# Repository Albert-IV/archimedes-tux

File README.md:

# Archimedes Tux Keyboard

Based off the excellent [Architeuthis Dux keyboard](https://github.com/tapioki/cephalopoda/tree/main/Architeuthis%20dux), the goal is to add a third thumb key and see where else this takes me.

Built with [Ergogen](https://github.com/mrzealot/ergogen).

##### Rev 0.1 - Working!

* AllPCB came back asking about the drilling holes.  Apparently one of them went through one of the TRRS pads, so I told them to just not cut that one out. The rest of the drilling holes are not through any pads or anything important
* PCB's shipped
* PCB's Arrived and Built
* Confirmed working via QMK!

## Rev 0.2

**WIP** - Currently only in `output` folder and completely unrouted.

## Ideas / Goals

- [ ] Make Pro Micro footprint reversible
  - [x]  Add footprint to repo
  - [x]  Rotate footprint
  - [ ]  Add representation of the USB cutout / area
  - [ ]  Change pads / silks to match Ergogen
  - [ ]  Convert Kicad footprint to Erogogen footprint
  - [ ]  Add PR to Erogogen
  - [ ]  Add / place on board
- [ ] Support [[Nice!Nano]] and (possibly) [[BlueMicro]]
  - [ ]  On / Off switch for battery 
  - [ ]  Add battery soldering pads to 
- [ ] Mousebites on third thumb key?
- [ ] Change routing in bottom area to allow for larger silkscreen eye

v0.1 -> v0.2

- [x] Swap pins on row connections to make routing easier
- [x] Add reset switch / pads
- [x] Fix edge cuts / drilling.  (Tapi believes this is an issue due to the multiple fillets / outlines in the Ergogen script)
- [x] Rename repo / files
- [x] Re-add solder locations for switches instead of only hotswap
- [x] Rotate thumbs to allow 1.5u / 2u keycaps
- [x] Re-add Puck support
  - [x]  Add initial footprint to library
  - [x]  Fix text when rotation makes the text apppear in the wrong order
  - [x]  Make each individual screw hole able to be turned on / off
  - [x]  Add PR to Erogogen
  - [x]  Add / place puck on board
- [x] Mousebites on TRRS jack (removable TRRS socket for better [[Nice!Nano]] support)
  - [x] Did it a different way, but the same applies

### To Run Locally

**If you do not have Node.js installed** 

Install using [the installer](https://nodejs.org/en/download/) [NVM,](https://github.com/nvm-sh/nvm) or [Chocolatey](https://community.chocolatey.org/packages/nodejs-lts) depending on your platform.  Using the installer usually leads to permission issues with NPM so it's suggested to use either NVM or chocolatey if you don't want to mess with it too much.

Once this is installed run `npm i -g npm` to upgrade NPM to the latest version.

**After Node.js is installed**

Run `npm run patch-footprints` in the base directory.  This is updates one of the footprints to allow for SMD or through-hole only diodes.

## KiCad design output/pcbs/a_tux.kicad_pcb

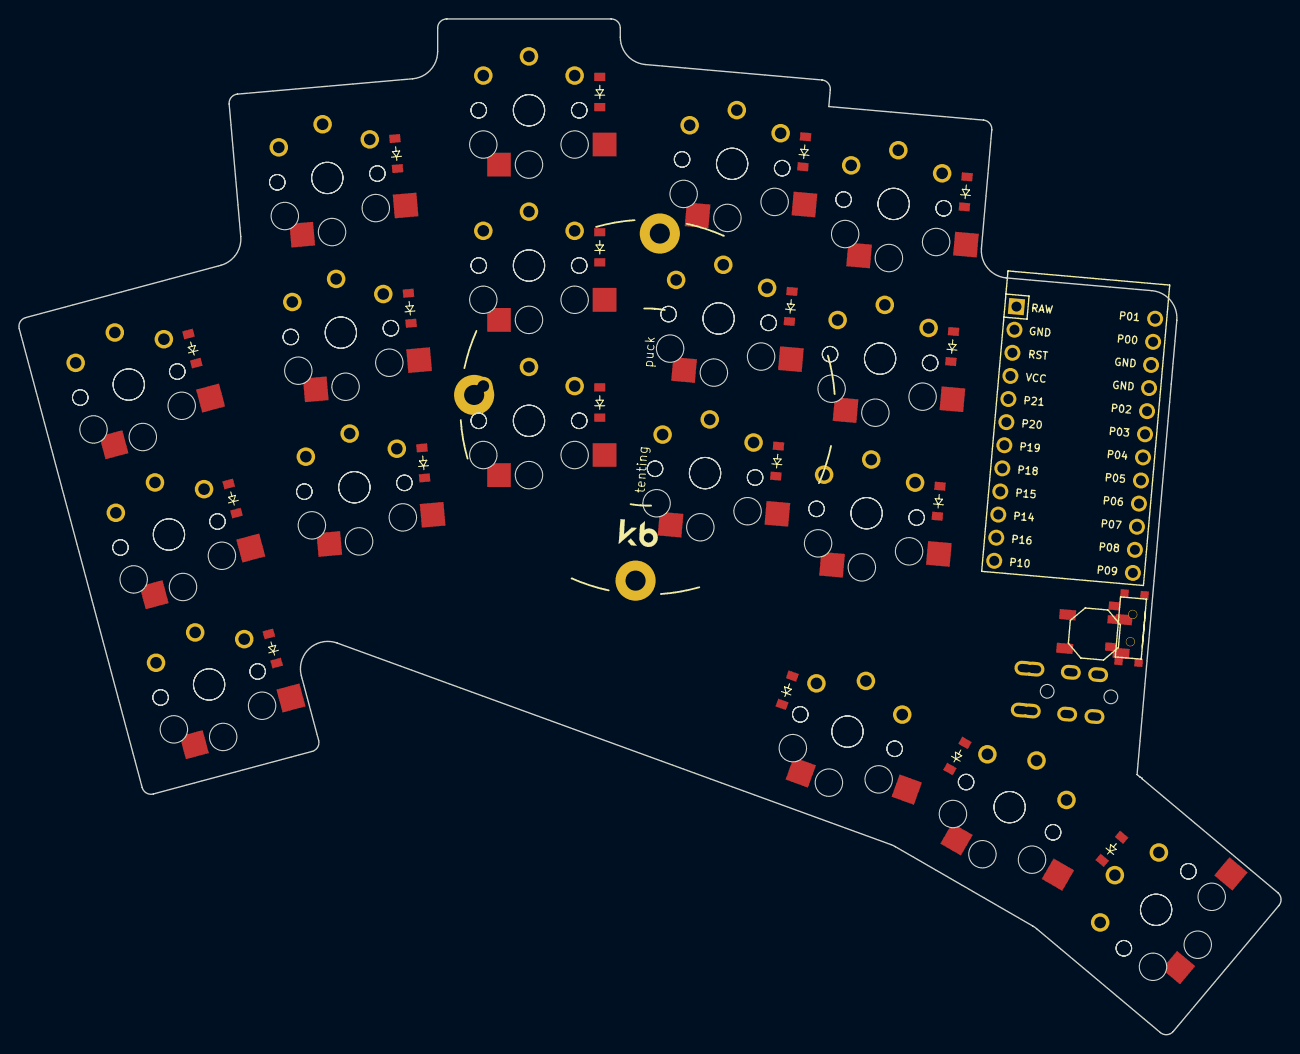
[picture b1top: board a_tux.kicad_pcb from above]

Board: 2 copper layers, 138.2 x 111.2 mm, 58 parts (0 on the bottom side), 29 nets, no tracks yet.

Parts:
B1: SW_TACT_ALPS_SKQGABE010
D1, D2, D3, D4, D5, D6, D7, D8, D9, D10, D11, D12, D13, D14, D15, D16, D17, D18: ComboDiode
MCU1: ProMicro
S1, S2, S3, S4, S5, S6, S7, S8, S9, S10, S11, S12, S13, S14, S15, S16, S17, S18, S19, S20, S21, S22, S23, S24, S25, S26, S27, S28, S29, S30, S31, S32, S33, S34, S35, S36: PG1350
T1: SPDT_C128955
_1: Tenting Puck

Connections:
GND: B1.1, MCU1.2, MCU1.15, MCU1.16, T1.1
P5: MCU1.20, S25.2, S26.2, S27.2, S28.2, S29.2, S30.2, S35.2, S36.2
P6: MCU1.21, S19.2, S20.2, S21.2, S22.2, S23.2, S24.2, S33.2, S34.2
P7: MCU1.22, S13.2, S14.2, S15.2, S16.2, S17.2, S18.2, S31.2, S32.2
P8: MCU1.23, S7.2, S8.2, S9.2, S10.2, S11.2, S12.2
P9: MCU1.24, S1.2, S2.2, S3.2, S4.2, S5.2, S6.2
P10: D3.1, D6.1, D9.1, D12.1, D15.1, MCU1.12
P14: D1.1, D4.1, D7.1, D10.1, D13.1, MCU1.10
P15: D16.1, D17.1, D18.1, MCU1.9
P16: D2.1, D5.1, D8.1, D11.1, D14.1, MCU1.11
RST: B1.2, MCU1.3
first_only: D16.2, S31.1, S32.1
index_bottom: D10.2, S19.1, S20.1
index_home: D11.2, S21.1, S22.1
index_top: D12.2, S23.1, S24.1
inner_bottom: D13.2, S25.1, S26.1
inner_home: D14.2, S27.1, S28.1
inner_top: D15.2, S29.1, S30.1
middle_bottom: D7.2, S13.1, S14.1
middle_home: D8.2, S15.1, S16.1
middle_top: D9.2, S17.1, S18.1
pinky_bottom: D1.2, S1.1, S2.1
pinky_home: D2.2, S3.1, S4.1
pinky_top: D3.2, S5.1, S6.1
ring_bottom: D4.2, S7.1, S8.1
ring_home: D5.2, S9.1, S10.1
ring_top: D6.2, S11.1, S12.1
second_only: D17.2, S33.1, S34.1
third_only: D18.2, S35.1, S36.1

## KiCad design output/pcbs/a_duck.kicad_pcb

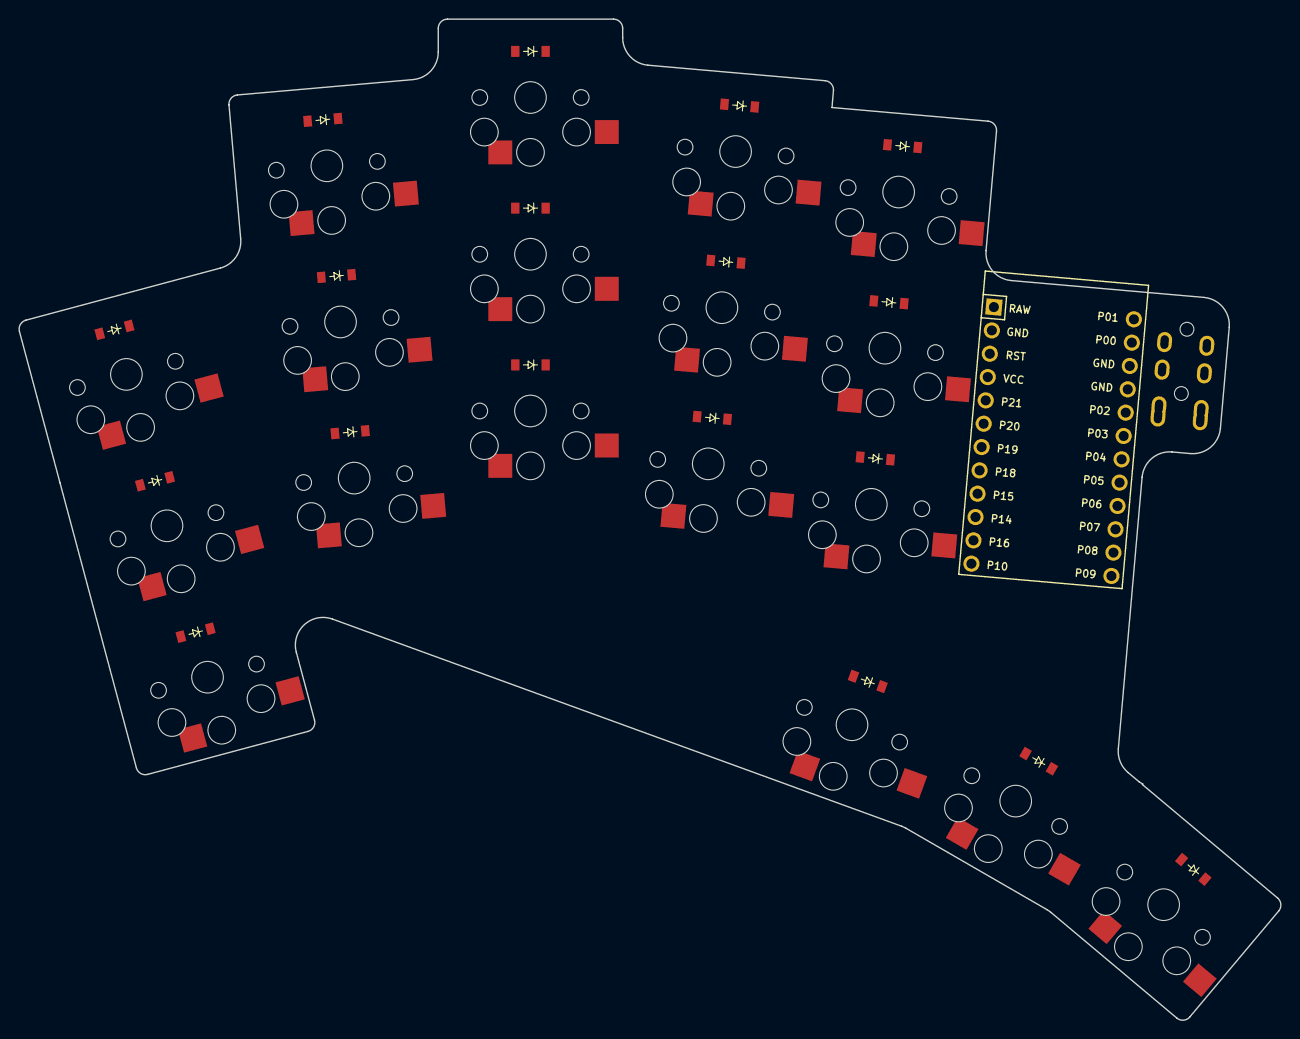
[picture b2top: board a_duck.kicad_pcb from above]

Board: 2 copper layers, 136.8 x 108.6 mm, 37 parts (0 on the bottom side), 28 nets, no tracks yet.

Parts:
D1, D2, D3, D4, D5, D6, D7, D8, D9, D10, D11, D12, D13, D14, D15, D16, D17, D18: ComboDiode
MCU1: ProMicro
S1, S2, S3, S4, S5, S6, S7, S8, S9, S10, S11, S12, S13, S14, S15, S16, S17, S18: PG1350

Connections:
GND: MCU1.2, MCU1.15, MCU1.16
P5: MCU1.20, S13.2, S14.2, S15.2, S18.2
P6: MCU1.21, S10.2, S11.2, S12.2, S17.2
P7: MCU1.22, S7.2, S8.2, S9.2, S16.2
P8: MCU1.23, S4.2, S5.2, S6.2
P9: MCU1.24, S1.2, S2.2, S3.2
P10: D3.1, D6.1, D9.1, D12.1, D15.1, MCU1.12
P14: D1.1, D4.1, D7.1, D10.1, D13.1, MCU1.10
P15: D16.1, D17.1, D18.1, MCU1.9
P16: D2.1, D5.1, D8.1, D11.1, D14.1, MCU1.11
first_only: D16.2, S16.1
index_bottom: D10.2, S10.1
index_home: D11.2, S11.1
index_top: D12.2, S12.1
inner_bottom: D13.2, S13.1
inner_home: D14.2, S14.1
inner_top: D15.2, S15.1
middle_bottom: D7.2, S7.1
middle_home: D8.2, S8.1
middle_top: D9.2, S9.1
pinky_bottom: D1.2, S1.1
pinky_home: D2.2, S2.1
pinky_top: D3.2, S3.1
ring_bottom: D4.2, S4.1
ring_home: D5.2, S5.1
ring_top: D6.2, S6.1
second_only: D17.2, S17.1
third_only: D18.2, S18.1

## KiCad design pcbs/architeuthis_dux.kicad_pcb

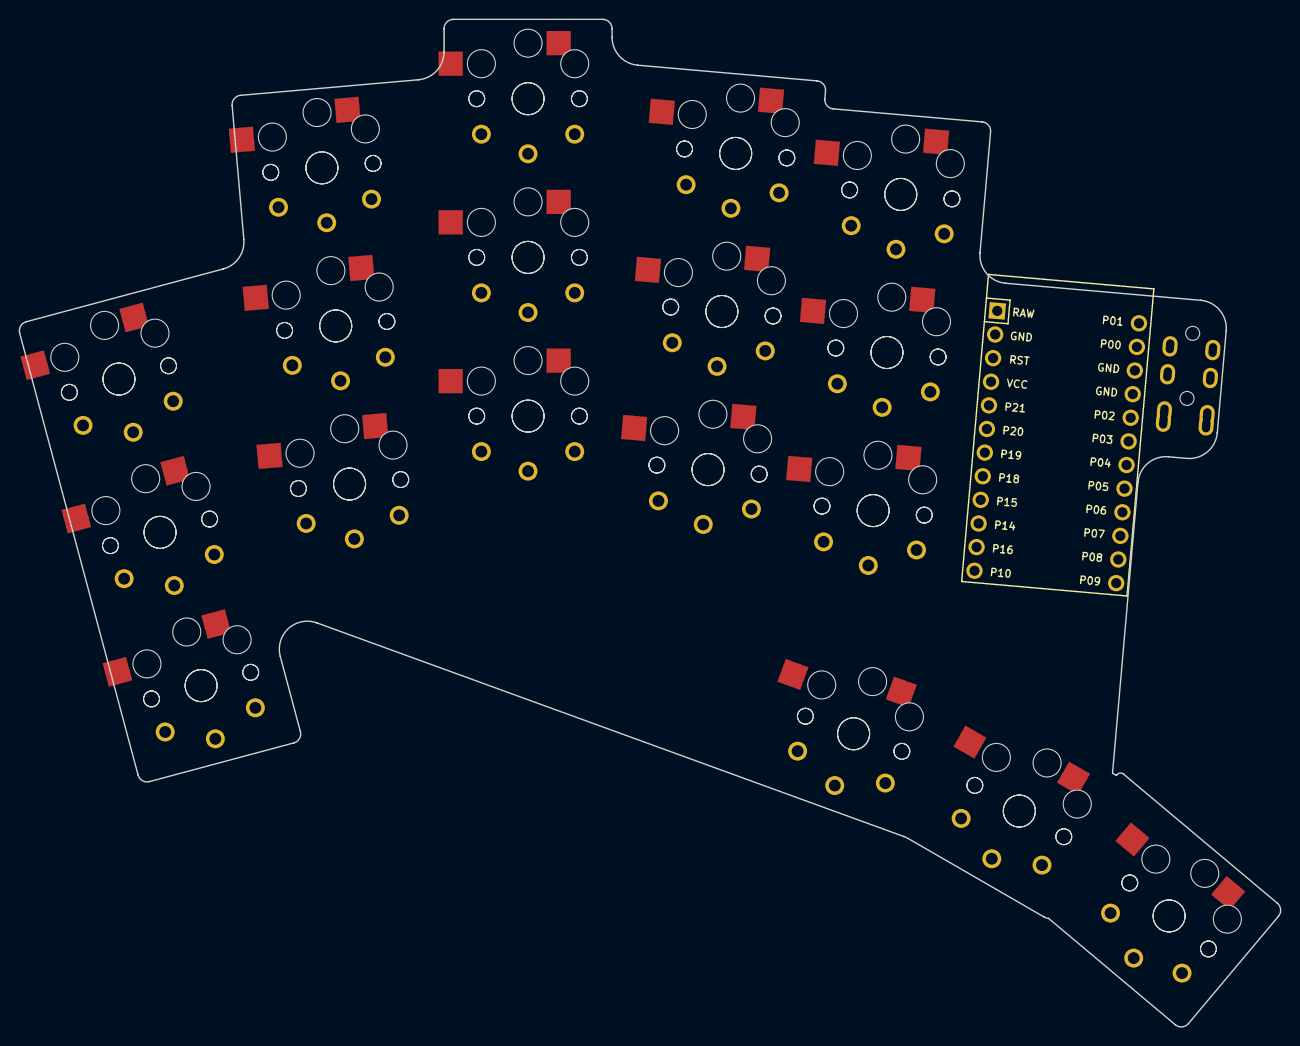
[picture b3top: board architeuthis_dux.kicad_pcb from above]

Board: 2 copper layers, 135.1 x 107.9 mm, 37 parts (0 on the bottom side), 18 nets, no tracks yet.

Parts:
MCU1: ProMicro
S1, S2, S3, S4, S5, S6, S7, S8, S9, S10, S11, S12, S13, S14, S15, S16, S17, S18, S19, S20, S21, S22, S23, S24, S25, S26, S27, S28, S29, S30, S31, S32, S33, S34, S35, S36: PG1350

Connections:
GND: MCU1.2, MCU1.15, MCU1.16, S1.2, S2.2, S3.2, S4.2, S5.2, S6.2, S7.2, S8.2, S9.2, S10.2, S11.2, S12.2, S13.2, S14.2, S15.2, S16.2, S17.2, S18.2, S19.2, S20.2, S21.2, S22.2, S23.2, S24.2, S25.2, S26.2, S27.2, S28.2, S29.2, S30.2, S31.2, S32.2, S33.2, S34.2, S35.2, S36.2
P0: MCU1.14, S11.1, S12.1
P1: MCU1.13, S13.1, S14.1
P3: MCU1.18, S9.1, S10.1
P4: MCU1.19, S7.1, S8.1
P5: MCU1.20, S5.1, S6.1
P6: MCU1.21, S3.1, S4.1
P7: MCU1.22, S1.1, S2.1
P8: MCU1.23, S31.1, S32.1
P9: MCU1.24, S33.1, S34.1
P10: MCU1.12, S25.1, S26.1, S35.1, S36.1
P14: MCU1.10, S21.1, S22.1
P15: MCU1.9, S19.1, S20.1
P16: MCU1.11, S23.1, S24.1
P18: MCU1.8, S17.1, S18.1
P19: MCU1.7, S15.1, S16.1
P20: MCU1.6, S27.1, S28.1
P21: MCU1.5, S29.1, S30.1

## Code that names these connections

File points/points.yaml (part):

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            - 0
        column_net: P7
        name: matrix_pinky_bottom
        colrow: pinky_bottom
        col: &ref_2
            spread: 18
            rotate: 15
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        bind: *ref_1
        column_net: P6
        name: matrix_pinky_home
        colrow: pinky_home
        col: *ref_2
        row: home
matrix_pinky_top:
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        bind: *ref_3
        column_net: P5
        name: matrix_pinky_top
        colrow: pinky_top
        col: *ref_2
        row: top
matrix_ring_bottom:
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
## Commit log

2021-08-13 Initial commit of WIP.
2021-08-13 Added README.md
2021-08-13 Remove unneeded zip file
2021-08-13 Remove the files put there by the .zip download
2021-08-13 Added more README info, sorted folders.
2021-08-16 Added diodes correctly, removed the non-hotswap locations for now. Added wiring 'guide' to help with setting up the wire map
2021-08-24 Got the key and diode matrix working!
2021-08-26 Patch diodes to be SMD only and rotate them for easier routing
2021-09-27 Added V1 of PCB with routing
2021-09-28 Added PCB silks and footprint files
2021-09-30 Sent PCB off to AllPCB
2021-10-02 Moved footprints to rev1 folder
2021-10-02 Updated wiring
2021-10-02 Fix outlines / edge cuts of PCB
2021-10-02 Fix left side pins for easier routing
2021-10-02 Added SMD reset button
2021-10-02 Remove commented area / code cleanup
2021-10-02 Rename files to move from A Duck -> Archimedes Tux
2021-10-03 Added hotswap + solder option for switches, moved diode locations, moved stuff around to make routing easier
2021-10-04 Rotated the outer thumb for 1.5u or 2u keycap.
2021-10-05 Added Split KB's Puck footprint
2021-10-09 Add puck back to the PCB, fix puck footprint. Added reversible header footprint
2021-10-09 Added PCB image
2021-10-10 Added additional row for Nice!Nano pinout
2021-10-21 Updated state of Rev1
2021-10-24 Added watch scripts, began moving TRRS / pro micro to give myself room
2021-10-24 Took care of TRRS problem, widened the pro micro space
2021-10-30 Removed reversible pro micro footprint, seems impossible to actually route
